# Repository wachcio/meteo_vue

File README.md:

# meteo_vue
System zbierania danych z kilkudziesięciu czujników. Zaczął powstawać w maju 2016 roku. Strona typu SPA powstaje od grudnia 2018 przy pomocy framework-a Vue.

Od jakiegoś czasu działał u mnie minikomputer Raspberry Pi z zainstalowanym Raspianem oraz systemem monitoringu temperatury (i nie tylko) Nettemp autorstwa techfreak. Mierzy on temperatury w kotłowni i na zewnątrz budynku za pomocą czujników DS18B20 oraz DHT22 (bardzo słabe i zawodne).

Po kilku miesiącach zacząłem myśleć nad własną stacją pogody która mogła by oprócz temperatur mierzyłć również inne parametry i co najważniejsze była mojego autorstwa. Dzięki pomocy ze strony forum Atnel oraz kanałowi YouTube Atnel - mirekk36 zaprojektowałem a następnie polutowałem urządzenie i zaprogramowałem w języku C mikrokontroler Atmega 32A który jest sercem stacji meteo. Stacja zbiera informacje z czujników: temperatury (DS18B20, BMP180, SHT21), wilgotności (SHT21), ciśnienia (BMP180), wiatru, opadów oraz nasłonecznienia (BH1750). 9 lutego 2020 zamieniłem czujnki SHT21 i BMP 180 na jeden BME280 który mierzy temperaturę, ciśnienie i wilgotność.

Zachęcony udaną budową stacji złożyłem projekt firmy Atnel opisany w żółtej książce Mirosława Kardasia czyli zegar w dwóch sztukach. Po modyfikacjach oprogramowania zegary znajdujące się w salonie oraz sypialni wysyłają dane do Raspberry Pi który zapisuje je w zewnętrznej bazie danych.

Kolejną małą częścią projektu stało się urządzenie oparte o znany moduł wi-fi ESP8266 do którego podłączyłem czujnik temperatury DS18B20 w hermetcznej obudowie i umieściłem w akwarium. On również wysyła swoje dane do Nettemp-a.

Ostatnim elementem układanki jest odpytywanie bazy danych Airly o dane z czujników jakości powietrza znajdującego się w mojej miejscowości (od maja 2021 dostępne są dwa czujniki).

Dane z wszystkich moich części systemu trafiają co minutę (dane jakości powietrza ze względu na ograniczenia AirlyAPI odczytywane są co kwadrans) do bazy danych MySQL umieszczonej na zewnętrznym serwerze. Odbywa się to za pośrednictwem napisanych przeze mnie skryptów PHP. Dopiero z tej bazy poprzez mój mini system Rest API czerpie informacje ta strona. Jeśli jest problem z danym czujnikiem i z jakiegoś powodu dane są starsze niż 5 minut (16 minut czujniki jakości powietrza) sygnalizowane to jest czerwoną obwódką wokół ikony czujnika. Po kliknięciu na czujnik pokazują się bardziej szczegółowe informacje. Natomist kliknięcie na tytuł kategorii powoduje jej ukrycie lub pokazanie.

## Demo
http://meteo.wachcio.pl/

## Project setup
```
npm install
```

### Compiles and hot-reloads for development
```
npm run serve
```

### Compiles and minifies for production
```
npm run build
```

### Run your tests
```
npm run test
```

### Lints and fixes files
```
npm run lint
```

### Customize configuration
See [Configuration Reference](https://cli.vuejs.org/config/).

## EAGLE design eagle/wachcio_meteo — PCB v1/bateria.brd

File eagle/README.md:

Projekt płytki PCB do urządzenia

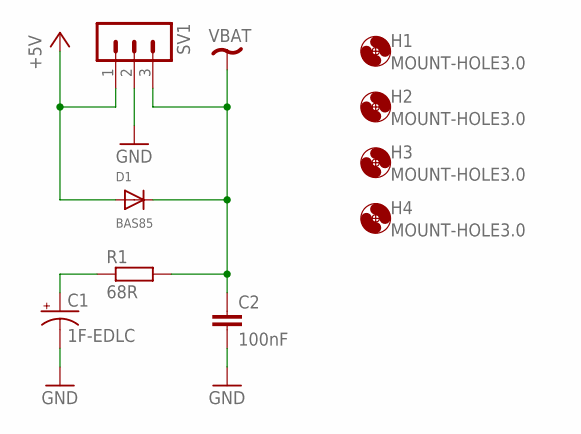
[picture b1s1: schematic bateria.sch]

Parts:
C1: 1F-EDLC; CAP-RADIAL-5MM-21.5MM
C2: 100nF; C0805
D1: BAS85; SMADIODE
H1, H2, H3, H4: MOUNT-HOLE3.0; 3,0
R1: 68R; R0805
SV1: MA03-1

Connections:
+5V: D1.A, SV1.1
GND: C1.-, C2.2, SV1.2
unnamed: C1.+, R1.1
VBAT: C2.1, D1.C, R1.2, SV1.3

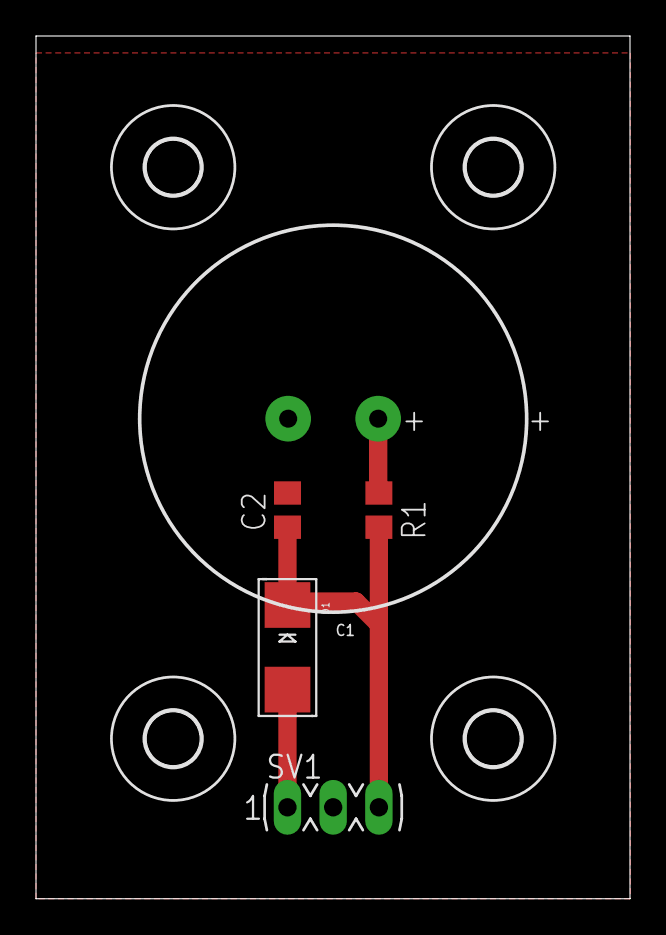
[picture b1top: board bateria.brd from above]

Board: 2 copper layers, 33.0 x 47.9 mm, 9 parts (0 on the bottom side), 4 nets.

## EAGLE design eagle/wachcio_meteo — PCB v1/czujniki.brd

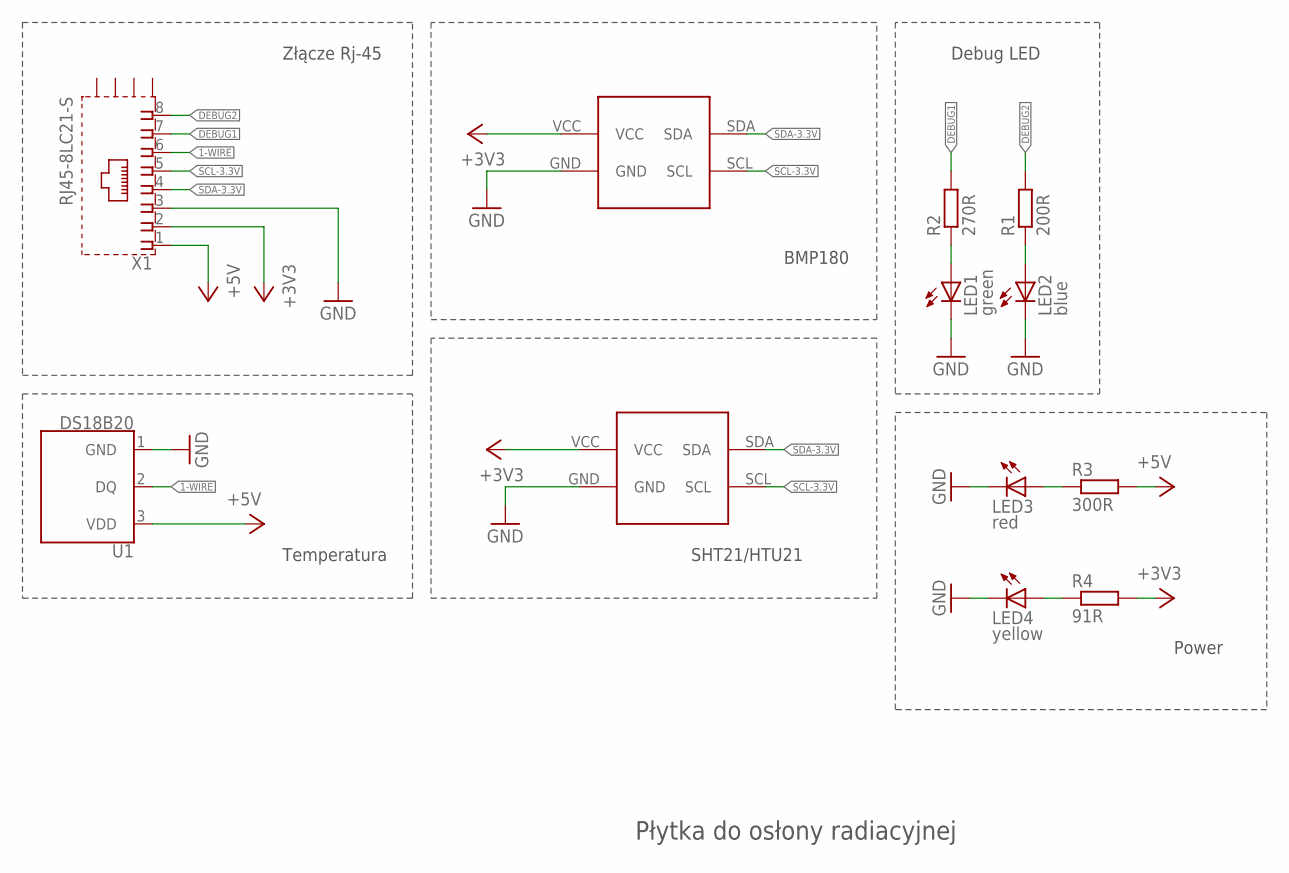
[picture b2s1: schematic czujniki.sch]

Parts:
LED1: green; CHIPLED_1206
LED2: blue; CHIPLED_1206
LED3: red; CHIPLED_1206
LED4: yellow; CHIPLED_1206
R1: 200R; M0805
R2: 270R; M0805
R3: 300R; M0805
R4: 91R; M0805
U1: DS18B20; TO-92-AMMO
U$1: BMP180
U$2: I2C_BOARD
X1: RJ45-8LC21-S; RJ45-SHIELD1

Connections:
1-WIRE: U1.2 (DQ), X1.6
+3V3: R4.2, U$1.VCC, U$2.VCC, X1.2
+5V: R3.2, U1.3 (VDD), X1.1
DEBUG1: R2.2, X1.7
DEBUG2: R1.2, X1.8
GND: LED1.C, LED2.C, LED3.C, LED4.C, U1.1 (GND), U$1.GND, U$2.GND, X1.3
unnamed: LED1.A, R2.1
unnamed: LED2.A, R1.1
unnamed: LED3.A, R3.1
unnamed: LED4.A, R4.1
SCL-3.3V: U$1.SCL, U$2.SCL, X1.5
SDA-3.3V: U$1.SDA, U$2.SDA, X1.4

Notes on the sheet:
BMP180
SHT21/HTU21
Złącze Rj-45
Temperatura
Debug LED
Płytka do osłony radiacyjnej
Power

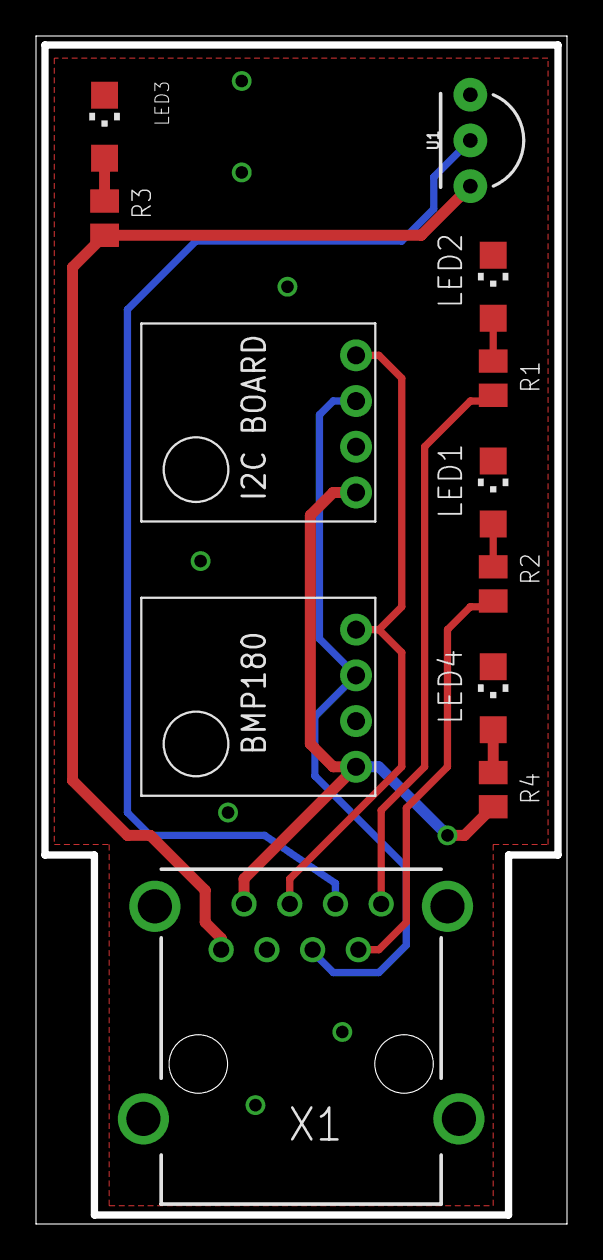
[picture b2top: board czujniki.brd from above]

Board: 2 copper layers, 29.5 x 66.0 mm, 12 parts (0 on the bottom side), 12 nets.

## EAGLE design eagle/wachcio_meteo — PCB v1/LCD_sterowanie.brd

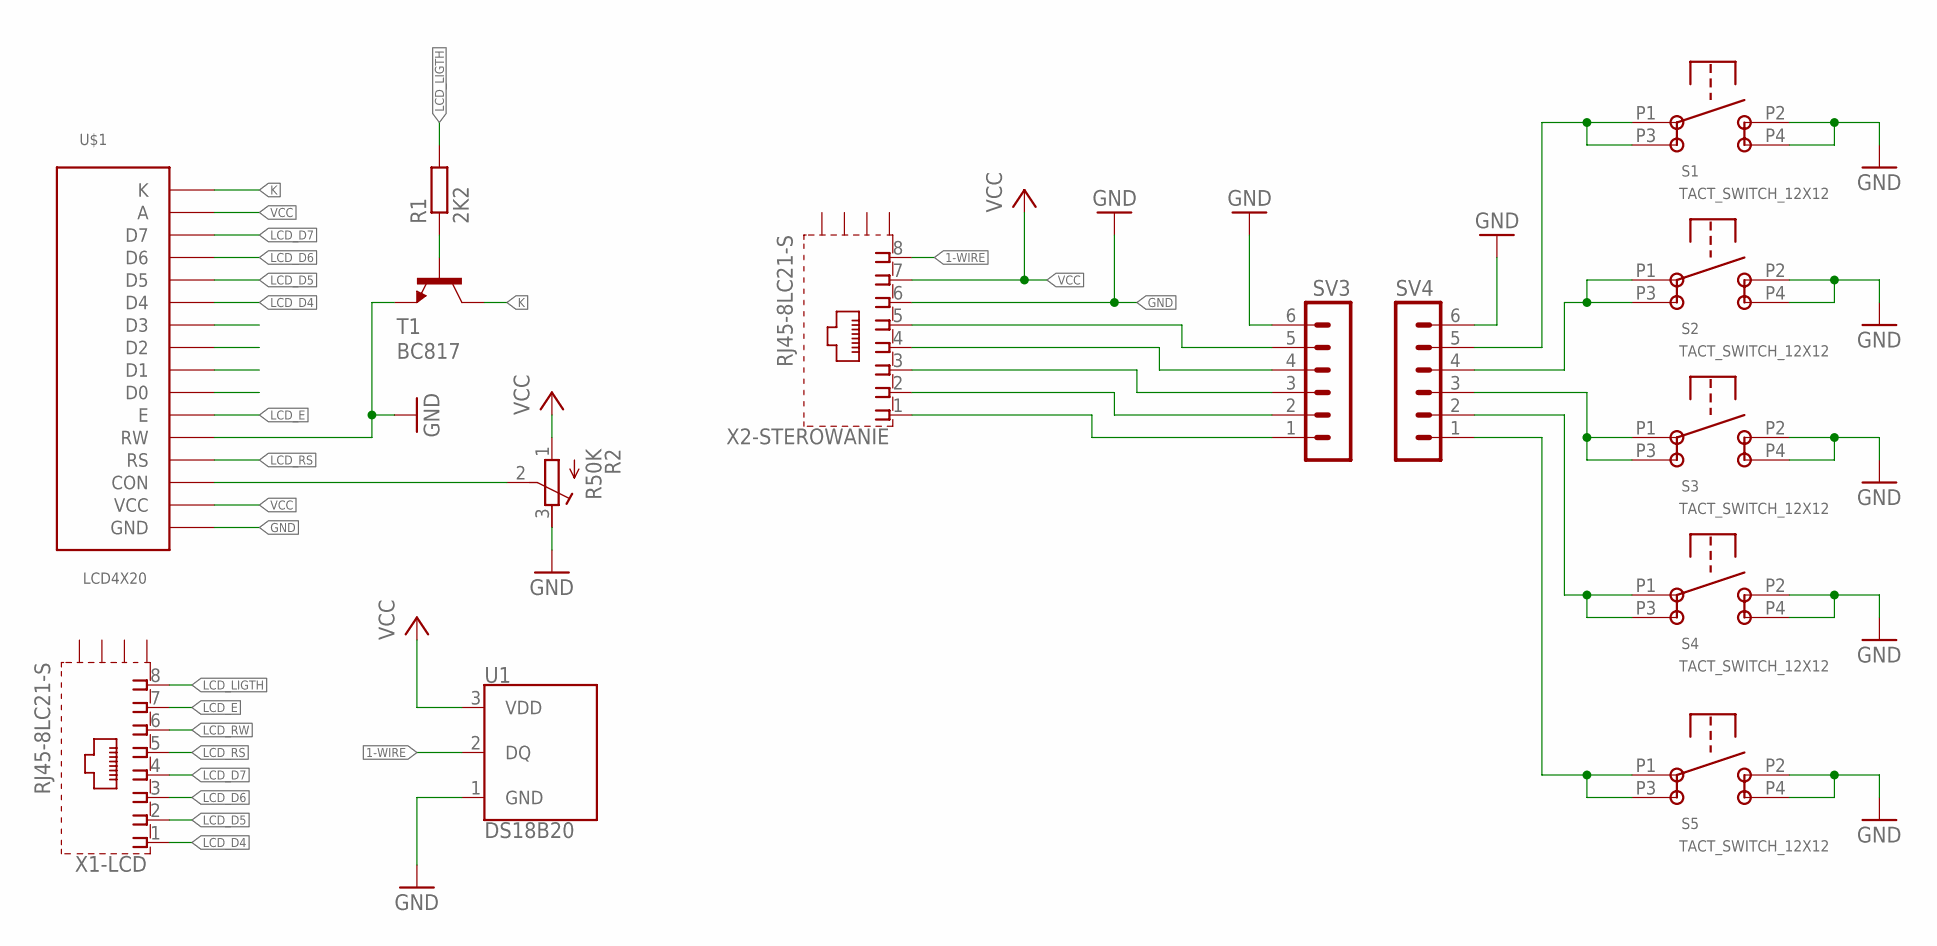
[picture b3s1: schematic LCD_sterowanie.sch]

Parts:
R1: 2K2; M0805
R2: R50K; RTRIM3296P
S1, S2, S3, S4, S5: TACT_SWITCH_12X12
SV3, SV4: MA06-1
T1: BC817; SOT23
U1: DS18B20; TO-92-AMMO
U$1: LCD4X20
X1-LCD, X2-STEROWANIE: RJ45-8LC21-S; RJ45-SHIELD1

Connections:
1-WIRE: U1.2 (DQ), X2-STEROWANIE.8
GND: R2.3 (E), S1.P2, S1.P4, S2.P2, S2.P4, S3.P2, S3.P4, S4.P2, S4.P4, S5.P2, S5.P4, SV3.6, SV4.6, T1.2 (E), U1.1 (GND), U$1.GND, U$1.RW, X2-STEROWANIE.6
K: T1.3 (C), U$1.K
LCD_D4: U$1.D4, X1-LCD.1
LCD_D5: U$1.D5, X1-LCD.2
LCD_D6: U$1.D6, X1-LCD.3
LCD_D7: U$1.D7, X1-LCD.4
LCD_E: U$1.E, X1-LCD.7
LCD_LIGTH: R1.2, X1-LCD.8
LCD_RS: U$1.RS, X1-LCD.5
LCD_RW: X1-LCD.6
unnamed: R1.1, T1.1 (B)
unnamed: S1.P1, S1.P3, SV4.5
unnamed: S2.P1, S2.P3, SV4.4
unnamed: S3.P1, S3.P3, SV4.3
unnamed: S4.P1, S4.P3, SV4.2
unnamed: S5.P1, S5.P3, SV4.1
unnamed: R2.2 (S), U$1.CON
S1: SV3.1, X2-STEROWANIE.1
S2: SV3.2, X2-STEROWANIE.2
S3: SV3.3, X2-STEROWANIE.3
S4: SV3.4, X2-STEROWANIE.4
S5: SV3.5, X2-STEROWANIE.5
VCC: R2.1 (A), U1.3 (VDD), U$1.A, U$1.VCC, X2-STEROWANIE.7

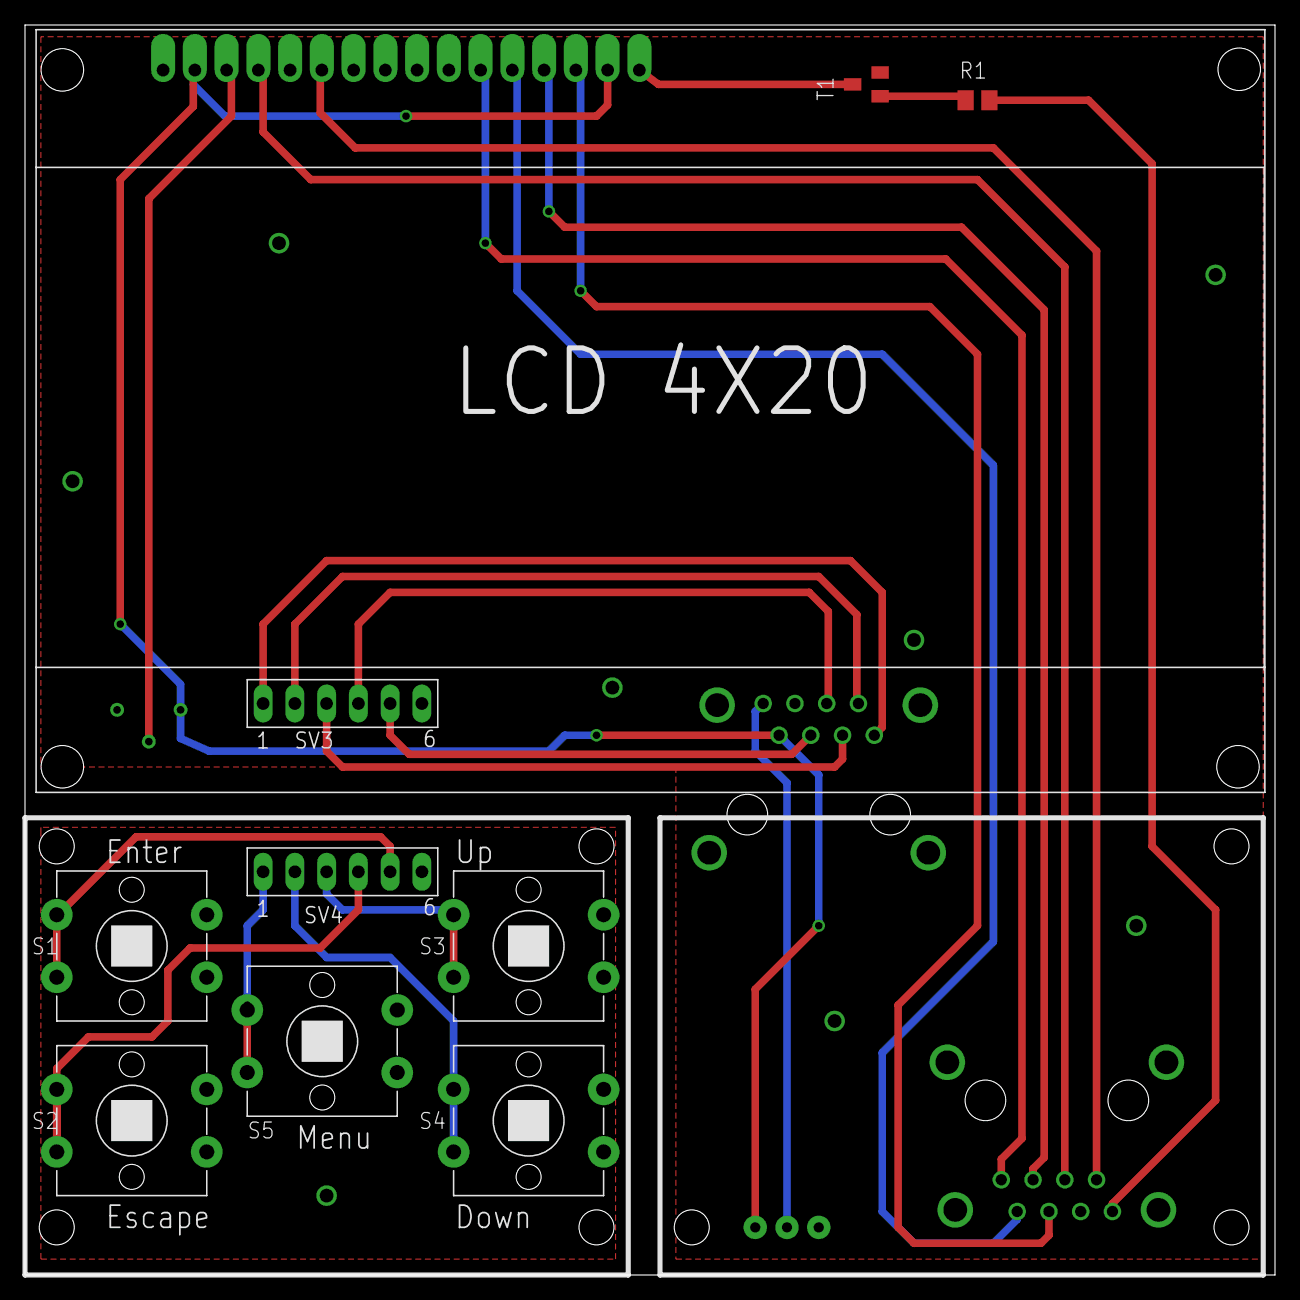
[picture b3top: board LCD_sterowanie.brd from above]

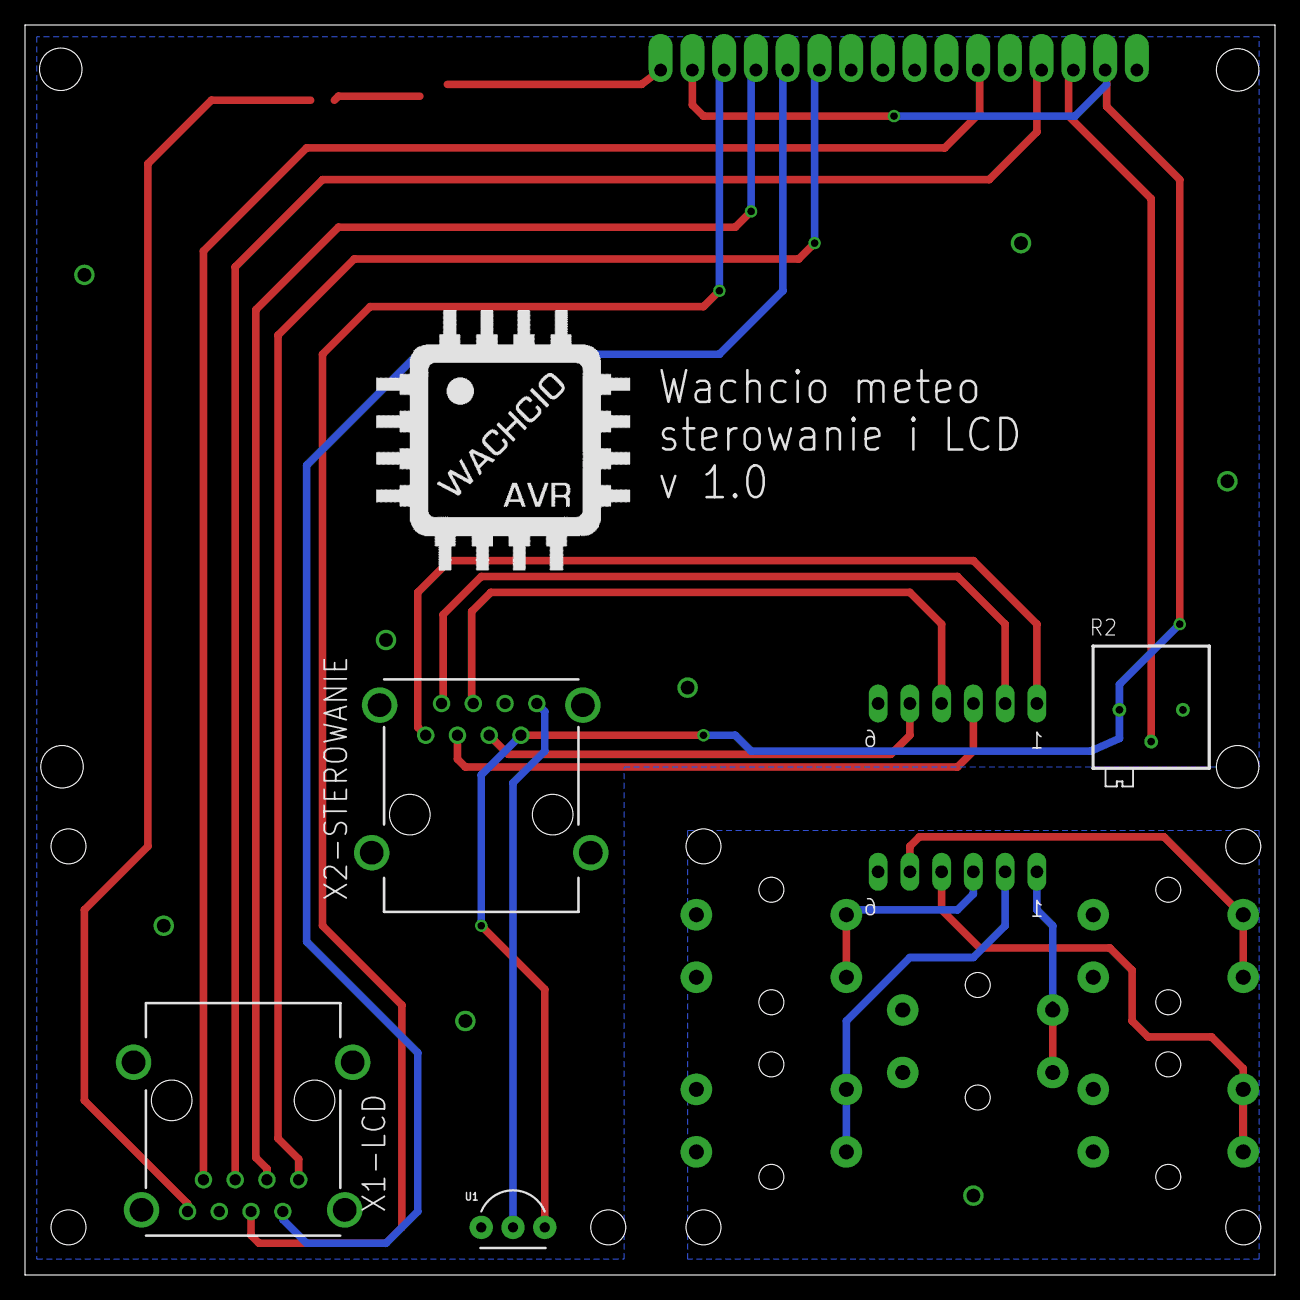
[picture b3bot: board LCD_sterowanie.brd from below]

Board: 2 copper layers, 100.0 x 100.0 mm, 15 parts (5 on the bottom side), 23 nets.

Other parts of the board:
U$2: LOGO

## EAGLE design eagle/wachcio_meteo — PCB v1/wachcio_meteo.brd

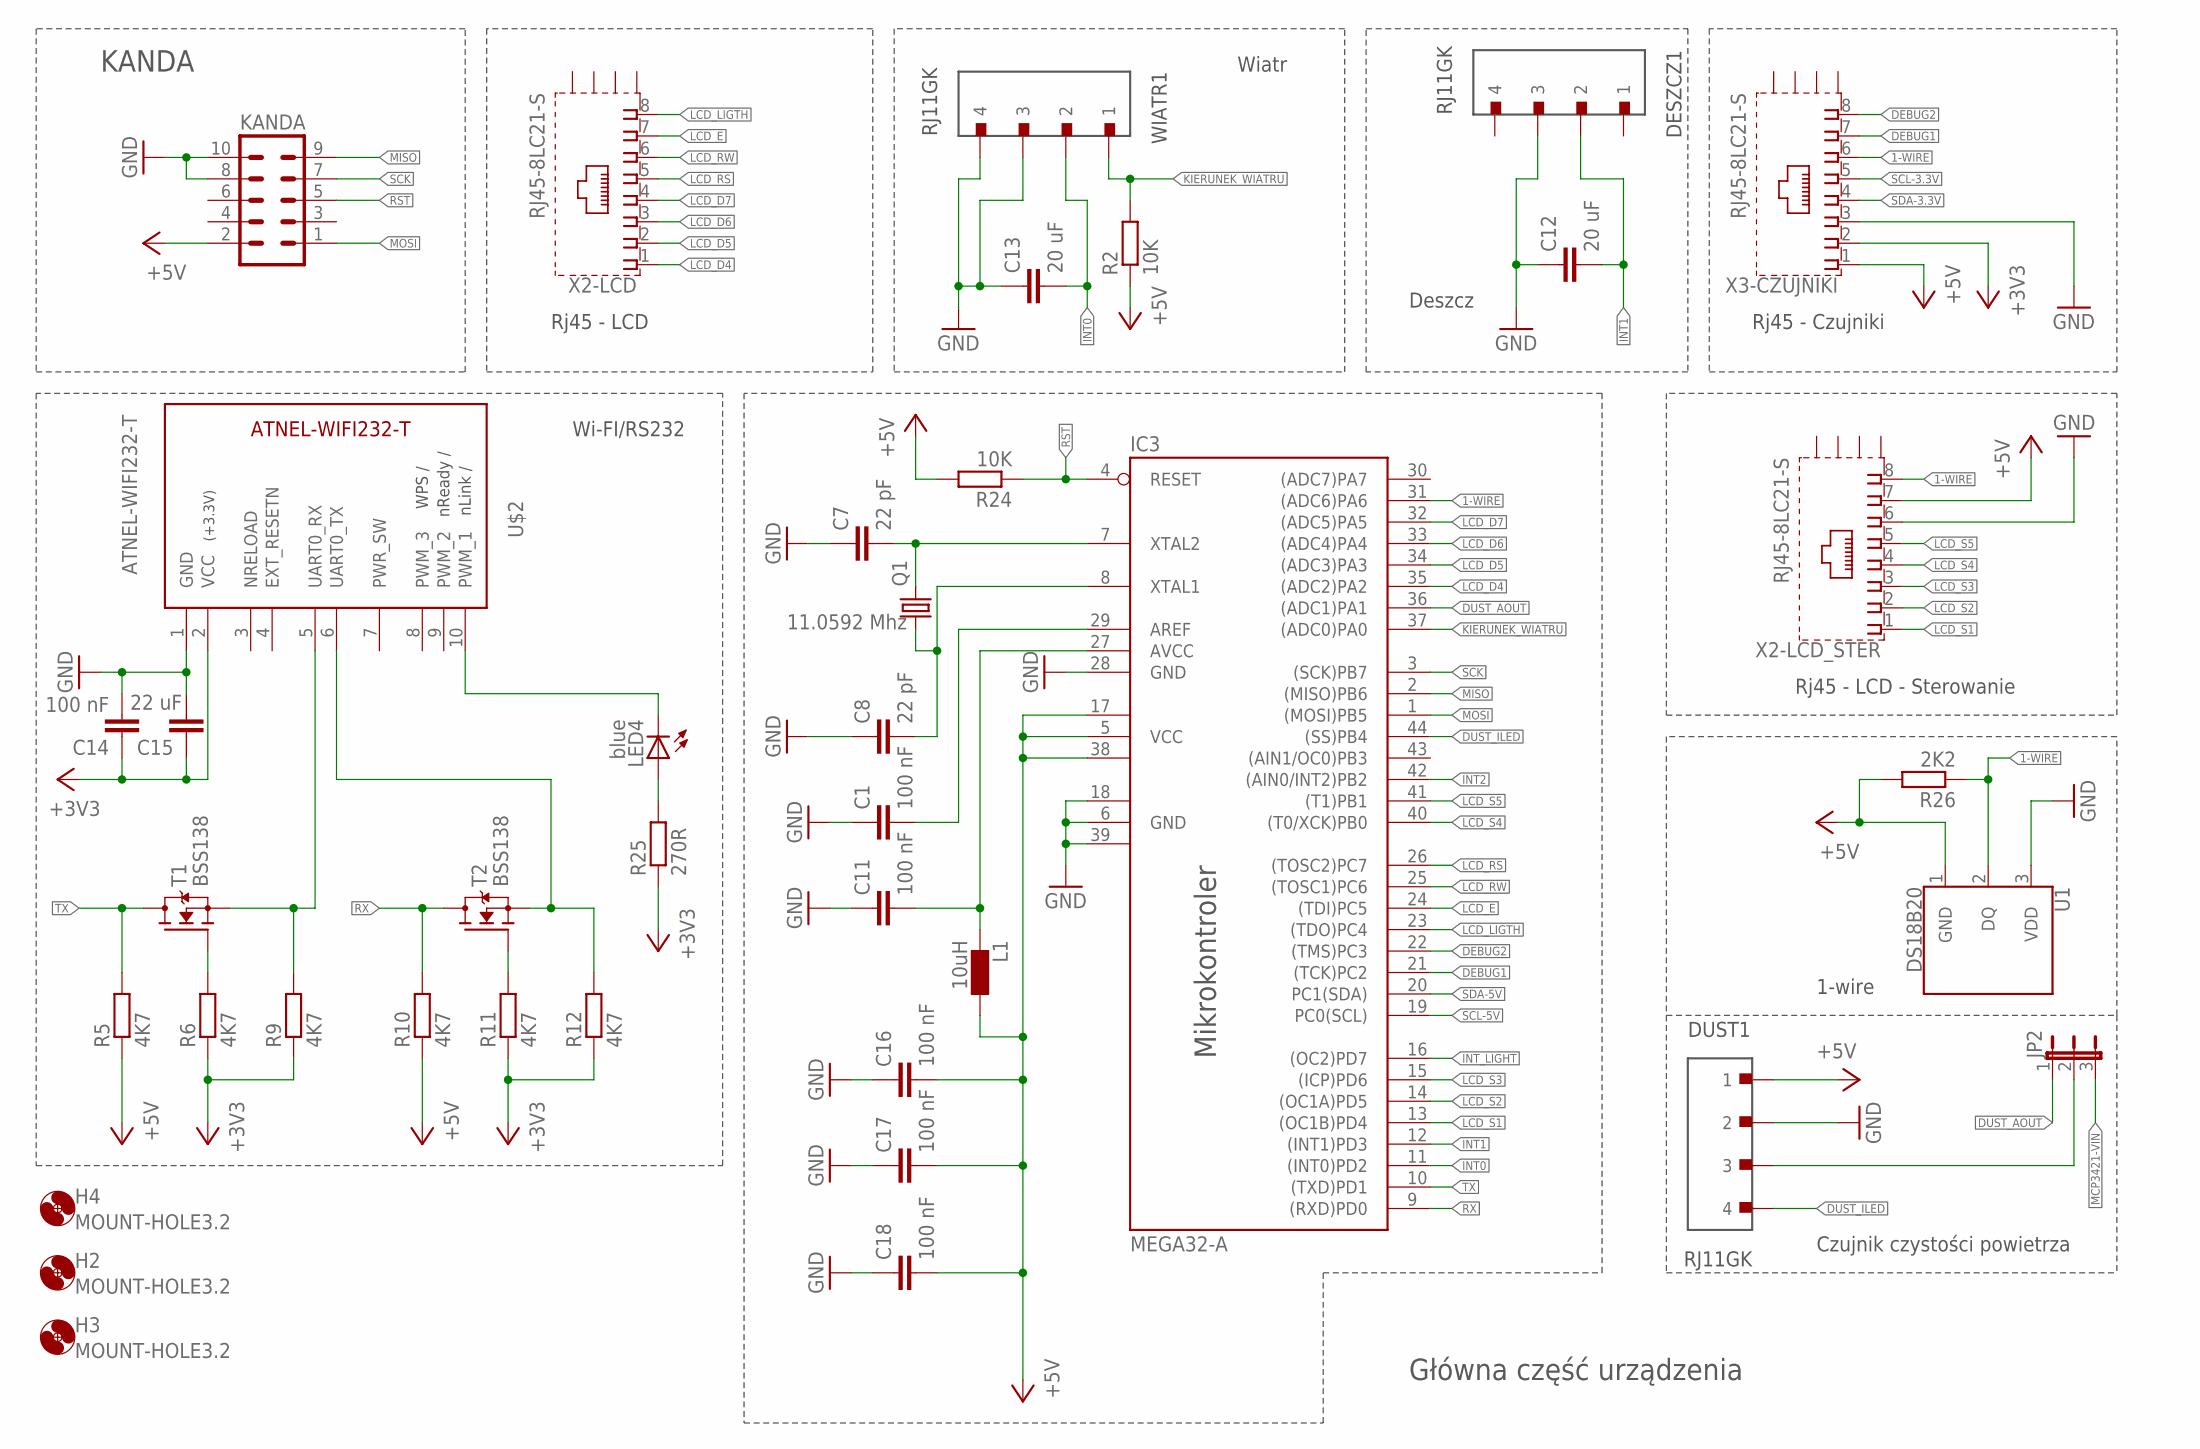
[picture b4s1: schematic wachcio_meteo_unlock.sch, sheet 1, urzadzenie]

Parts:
C1, C11, C14, C16, C17, C18: 100 nF; C0805
C7, C8: 22 pF; C0805
C12, C13: 20 uF; C0805
C15: 22 uF; C0805
DESZCZ1: RJ11GK
DUST1: RJ11GK
H2, H3, H4: MOUNT-HOLE3.2; 3,2
IC3: MEGA32-A; TQFP44
JP2: JP2E; JP2
KANDA: ML10
L1: 10uH; L3230M
LED4: blue; CHIPLED_1206
Q1: 11.0592 Mhz; SM49
R2, R24: 10K; M0805
R5, R6, R9, R10, R11, R12: 4K7; M0805
R25: 270R; M0805
R26: 2K2; M0805
T1, T2: BSS138; SOT23
U1: DS18B20; TO-92-AMMO
U$2: ATNEL-WIFI232-T
WIATR1: RJ11GK
X2-LCD, X2-LCD_STER, X3-CZUJNIKI: RJ45-8LC21-S; RJ45-SHIELD1

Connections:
1-WIRE: IC3.31 ((ADC6)PA6), R26.1, U1.2 (DQ), X2-LCD_STER.8, X3-CZUJNIKI.6
+3V3: C14.1, C15.1, R6.1, R9.1, R11.1, R12.1, R25.1, U$2.2 (VCC), X3-CZUJNIKI.2; also elsewhere on the board
+5V: C16.2, C17.2, C18.2, DUST1.1, IC3.5 (VCC), IC3.17 (VCC1), IC3.38 (VCC2), KANDA.2, L1.1, R2.1, R5.1, R10.1, R24.2, R26.2, U1.1 (GND), X2-LCD_STER.7, X3-CZUJNIKI.1; also elsewhere on the board
DEBUG1: IC3.21 ((TCK)PC2), X3-CZUJNIKI.7
DEBUG2: IC3.22 ((TMS)PC3), X3-CZUJNIKI.8
DUST_AOUT: IC3.36 ((ADC1)PA1), JP2.1
DUST_ILED: DUST1.4, IC3.44 ((SS)PB4)
GND: C1.1, C7.1, C8.1, C11.1, C12.1, C13.1, C14.2, C15.2, C16.1, C17.1, C18.1, DESZCZ1.3, DUST1.2, IC3.6 (GND), IC3.18 (GND1), IC3.28 (GND), IC3.39 (GND2), KANDA.8, KANDA.10, U1.3 (VDD), U$2.1 (GND), WIATR1.3, WIATR1.4, X2-LCD_STER.6, X3-CZUJNIKI.3; also elsewhere on the board
INT0: C13.2, IC3.11 ((INT0)PD2), WIATR1.2
INT1: C12.2, DESZCZ1.2, IC3.12 ((INT1)PD3)
INT2: IC3.42 ((AIN0/INT2)PB2); also elsewhere on the board
INT_LIGHT: IC3.16 ((OC2)PD7); also elsewhere on the board
KIERUNEK_WIATRU: IC3.37 ((ADC0)PA0), R2.2, WIATR1.1
LCD_D4: IC3.35 ((ADC2)PA2), X2-LCD.1
LCD_D5: IC3.34 ((ADC3)PA3), X2-LCD.2
LCD_D6: IC3.33 ((ADC4)PA4), X2-LCD.3
LCD_D7: IC3.32 ((ADC5)PA5), X2-LCD.4
LCD_E: IC3.24 ((TDI)PC5), X2-LCD.7
LCD_LIGTH: IC3.23 ((TDO)PC4), X2-LCD.8
LCD_RS: IC3.26 ((TOSC2)PC7), X2-LCD.5
LCD_RW: IC3.25 ((TOSC1)PC6), X2-LCD.6
LCD_S1: IC3.13 ((OC1B)PD4), X2-LCD_STER.1
LCD_S2: IC3.14 ((OC1A)PD5), X2-LCD_STER.2
LCD_S3: IC3.15 ((ICP)PD6), X2-LCD_STER.3
LCD_S4: IC3.40 ((T0/XCK)PB0), X2-LCD_STER.4
LCD_S5: IC3.41 ((T1)PB1), X2-LCD_STER.5
MCP3421-VIN: JP2.3; also elsewhere on the board
MISO: IC3.2 ((MISO)PB6), KANDA.9
MOSI: IC3.1 ((MOSI)PB5), KANDA.1
unnamed: R9.2, T1.2 (S), U$2.5 (UART0_RX)
unnamed: C11.2, IC3.27 (AVCC), L1.2
unnamed: C1.2, IC3.29 (AREF)
unnamed: LED4.A, R25.2
unnamed: R6.2, T1.1 (G)
unnamed: LED4.C, U$2.10 (PWM_1)
unnamed: R12.2, T2.2 (S), U$2.6 (UART0_TX)
unnamed: C7.2, IC3.7 (XTAL2), Q1.2
unnamed: C8.2, IC3.8 (XTAL1), Q1.1
unnamed: DUST1.3, JP2.2
unnamed: R11.2, T2.1 (G)
RST: IC3.4 (RESET), KANDA.5, R24.1
RX: IC3.9 ((RXD)PD0), R10.2, T2.3 (D)
SCK: IC3.3 ((SCK)PB7), KANDA.7
SCL-3.3V: X3-CZUJNIKI.5; also elsewhere on the board
SCL-5V: IC3.19 (PC0(SCL)); also elsewhere on the board
SDA-3.3V: X3-CZUJNIKI.4; also elsewhere on the board
SDA-5V: IC3.20 (PC1(SDA)); also elsewhere on the board
TX: IC3.10 ((TXD)PD1), R5.2, T1.3 (D)

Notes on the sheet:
KANDA
Mikrokontroler
Rj45 - LCD
Wiatr
Deszcz
Rj45 - Czujniki
Wi-FI/RS232
1-wire
Rj45 - LCD - Sterowanie
Główna część urządzenia
Czujnik czystości powietrza

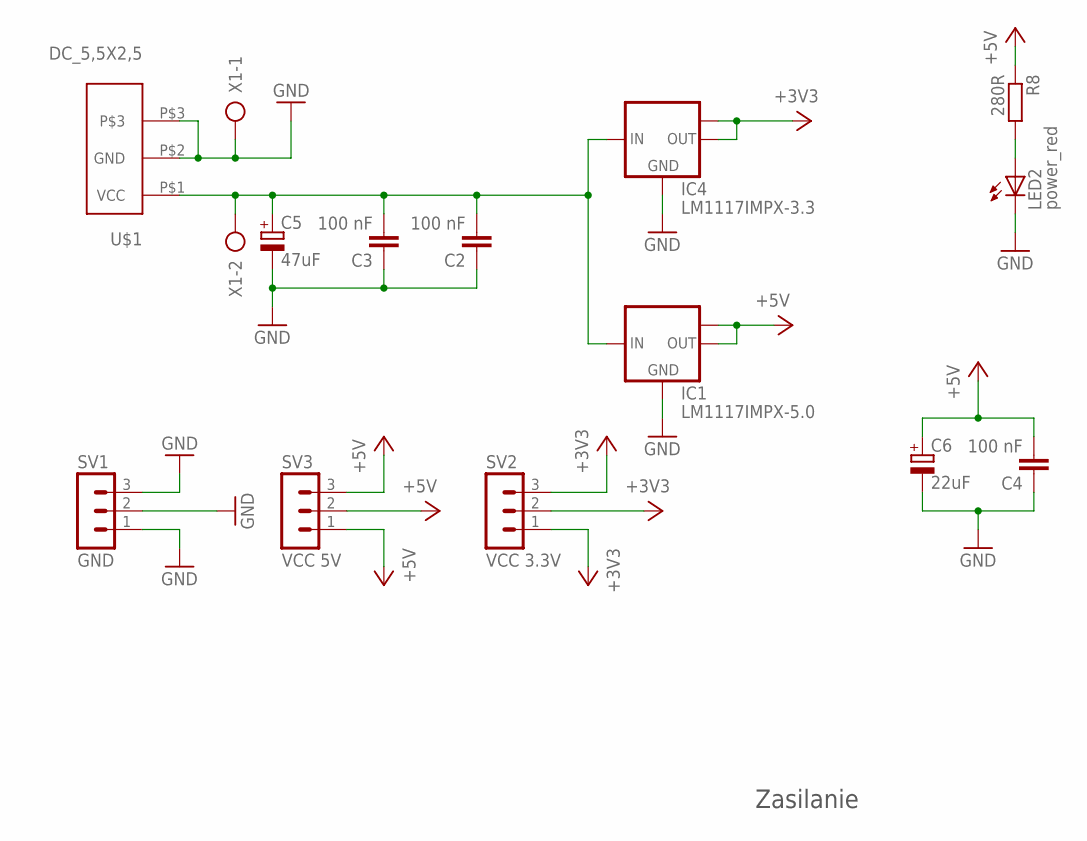
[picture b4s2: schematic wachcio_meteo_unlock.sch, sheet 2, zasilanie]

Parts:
C2, C3, C4: 100 nF; C0805
C5: 47uF; B45181A
C6: 22uF; B45181A
IC1: LM1117IMPX-5.0; SOT223
IC4: LM1117IMPX-3.3; SOT223
LED2: power_red; CHIPLED_1206
R8: 280R; M0805
SV1: GND; MA03-1
SV2: VCC 3.3V; MA03-1
SV3: VCC 5V; MA03-1
U$1: DC_5,5X2,5
X1: AK500/2

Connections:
+3V3: IC4.2 (OUT), IC4.TAB (OUT1), SV2.1, SV2.2, SV2.3; also elsewhere on the board
+5V: C4.2, C6.+, IC1.2 (OUT), IC1.TAB (OUT1), R8.1, SV3.1, SV3.2, SV3.3; also elsewhere on the board
+9V: C2.2, C3.2, C5.+, IC1.3 (IN), IC4.3 (IN), U$1.P$1 (VCC), X1.2
GND: C2.1, C3.1, C4.1, C5.-, C6.-, IC1.1 (GND), IC4.1 (GND), LED2.C, SV1.1, SV1.2, SV1.3, U$1.P$2 (GND), U$1.P$3, X1.1; also elsewhere on the board
unnamed: LED2.A, R8.2

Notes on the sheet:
Zasilanie

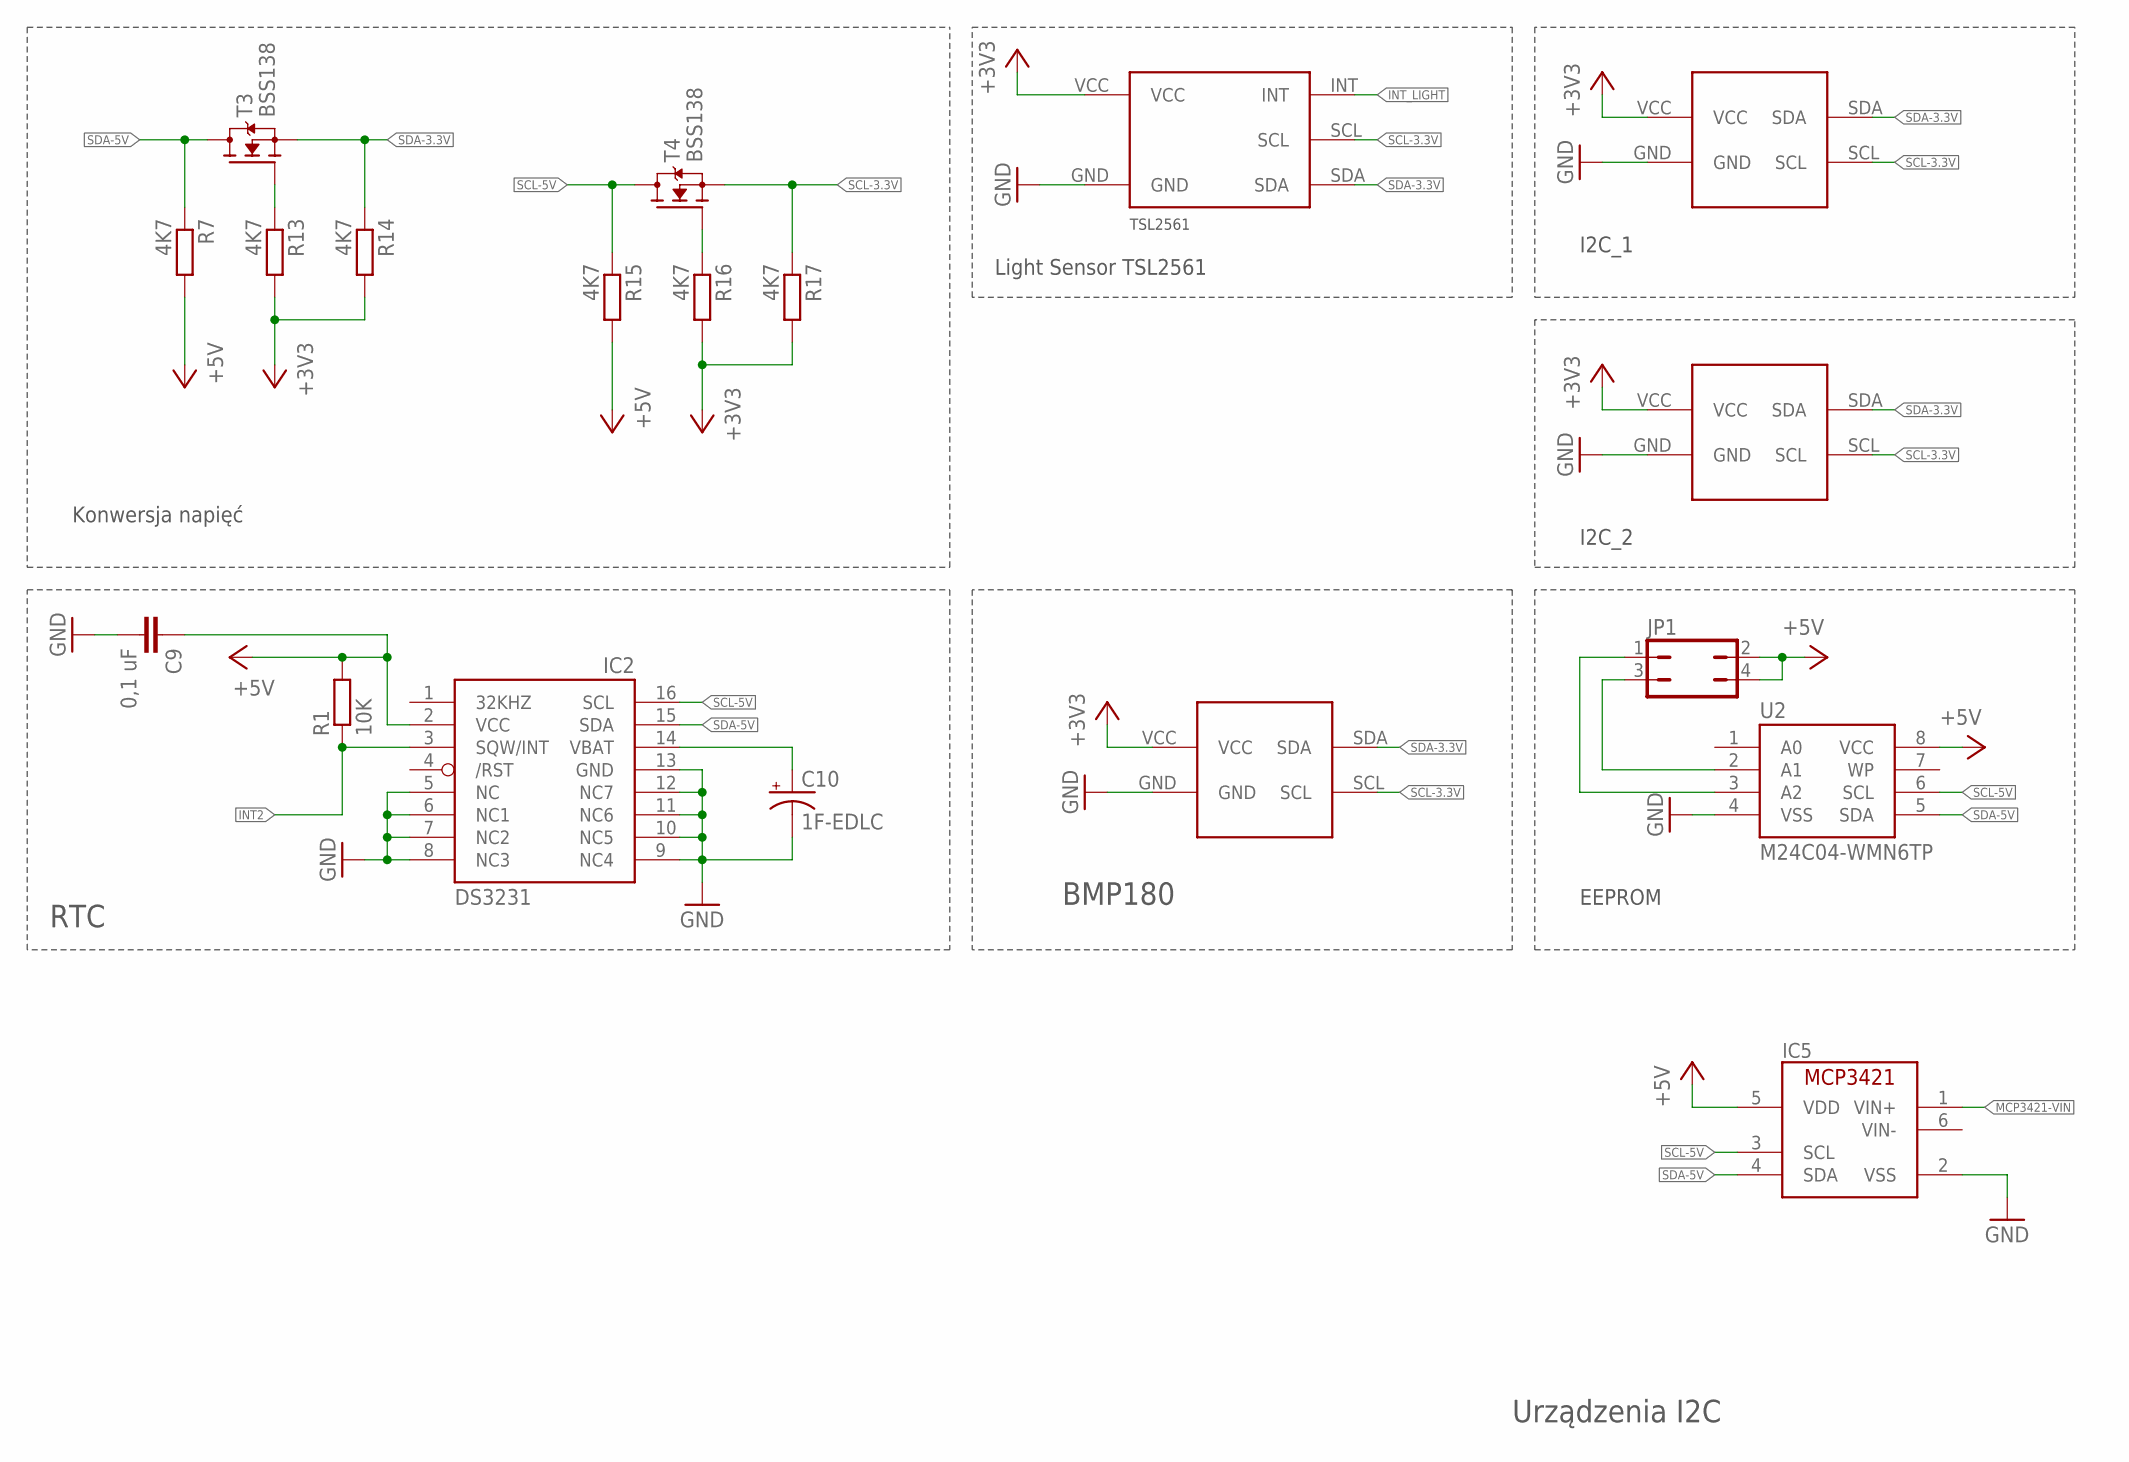
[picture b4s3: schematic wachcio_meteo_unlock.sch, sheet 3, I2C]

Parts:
C9: 0,1 uF; C0805
C10: 1F-EDLC; CAP-RADIAL-5MM-21.5MM
IC2: DS3231/SO; SO16W
IC5: MCP3421; SOT-23
JP1: JP2Q
R1: 10K; M0805
R7, R13, R14, R15, R16, R17: 4K7; M0805
T3, T4: BSS138; SOT23
U2: M24C04-WMN6TP; SO08
U$3: BMP180
U$5, U$6: I2C_BOARD
U$7: TSL2561GY-2561; TSL2561

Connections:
+3V3: R13.2, R14.2, R16.2, R17.2, U$3.VCC, U$5.VCC, U$6.VCC, U$7.VCC; also elsewhere on the board
+5V: C9.1, IC2.2 (VCC), IC5.5 (VDD), JP1.2, JP1.4, R1.2, R7.2, R15.2, U2.8 (VCC); also elsewhere on the board
GND: C9.2, C10.-, IC2.5 (NC), IC2.6 (NC1), IC2.7 (NC2), IC2.8 (NC3), IC2.9 (NC4), IC2.10 (NC5), IC2.11 (NC6), IC2.12 (NC7), IC2.13 (GND), IC5.2 (VSS), U2.4 (VSS), U$3.GND, U$5.GND, U$6.GND, U$7.GND; also elsewhere on the board
INT2: IC2.3 (SQW/INT), R1.1; also elsewhere on the board
INT_LIGHT: U$7.INT; also elsewhere on the board
MCP3421-VIN: IC5.1 (VIN+); also elsewhere on the board
unnamed: C10.+, IC2.14 (VBAT)
unnamed: R13.1, T3.1 (G)
unnamed: R16.1, T4.1 (G)
unnamed: JP1.3, U2.2 (A1)
unnamed: JP1.1, U2.3 (A2)
SCL-3.3V: R17.1, T4.2 (S), U$3.SCL, U$5.SCL, U$6.SCL, U$7.SCL; also elsewhere on the board
SCL-5V: IC2.16 (SCL), IC5.3 (SCL), R15.1, T4.3 (D), U2.6 (SCL); also elsewhere on the board
SDA-3.3V: R14.1, T3.2 (S), U$3.SDA, U$5.SDA, U$6.SDA, U$7.SDA; also elsewhere on the board
SDA-5V: IC2.15 (SDA), IC5.4 (SDA), R7.1, T3.3 (D), U2.5 (SDA); also elsewhere on the board

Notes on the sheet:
Konwersja napięć
RTC
BMP180
I2C_1
I2C_2
EEPROM
Light Sensor TSL2561
Urządzenia I2C

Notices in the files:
parts and their libraries:
SparkFun-Sensors: Licensing: Creative Commons ShareAlike 4.0 International - https://creativecommons.org/licenses/by-sa/4.0
supply2: Copyright (C) 2007, Bob Starr
FaBo-Sensor: Released under the Creative Commons Attribution-ShareAlike 4.0 License
https://creativecommons.org/licenses/by-sa/4.0
